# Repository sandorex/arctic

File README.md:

## Arctic

Arctic (**A**i**r** **C**ondi**ti**oner **C**ycler) is a dumb little device that basically cycles your air conditioner using the IR signal

### What?
Its just a dumb little device that turns the AC on or off based on a time delay using IR

Oversized AC units are a nightmare, so this was the best and cheapest solution

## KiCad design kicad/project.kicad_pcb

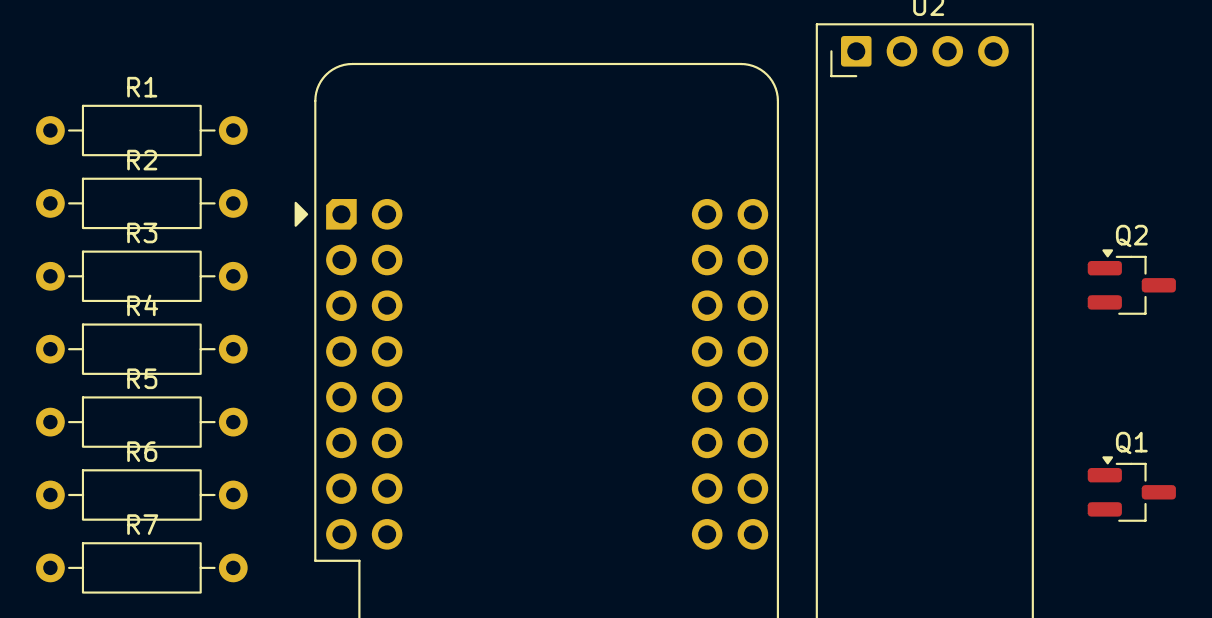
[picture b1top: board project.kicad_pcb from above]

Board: 2 copper layers, 11 parts (0 on the bottom side), 6 nets, no tracks yet.

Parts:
Q1: AO3402; SOT-23_Handsoldering
Q2: AO3401; SOT-23_Handsoldering
R1, R4: 10K; R_Axial_DIN0207_L6.3mm_D2.5mm_P10.16mm_Horizontal
R2: 33; R_Axial_DIN0207_L6.3mm_D2.5mm_P10.16mm_Horizontal
R3, R5: 1K; R_Axial_DIN0207_L6.3mm_D2.5mm_P10.16mm_Horizontal
R6, R7: 100K; R_Axial_DIN0207_L6.3mm_D2.5mm_P10.16mm_Horizontal
U1: WEMOS_ESP32_S2_Mini; WEMOS_S2_mini
U2: I2C 0.91 128x32 OLED; ER_OLEDM0.91_1x-I2C

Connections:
/BAT_SENSE: R6.1, R7.2, U1.17 (ADC2_6)
/IR_LED: R3.2, U1.15 (GPIO15)
GND: R1.1, R7.1, U2.1 (GND)
unnamed: R1.2, R3.1
unnamed: R4.2, R5.1
VCC: R6.2, U2.2 (VCC)
